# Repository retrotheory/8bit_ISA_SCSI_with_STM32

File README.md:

# 8bit_ISA_SCSI_with_STM32
ISA SCSI card with BIOS and spot of software SCSI emulation with STM32

SCSI card designed from the NCR53C400 Technical Document

More details to come

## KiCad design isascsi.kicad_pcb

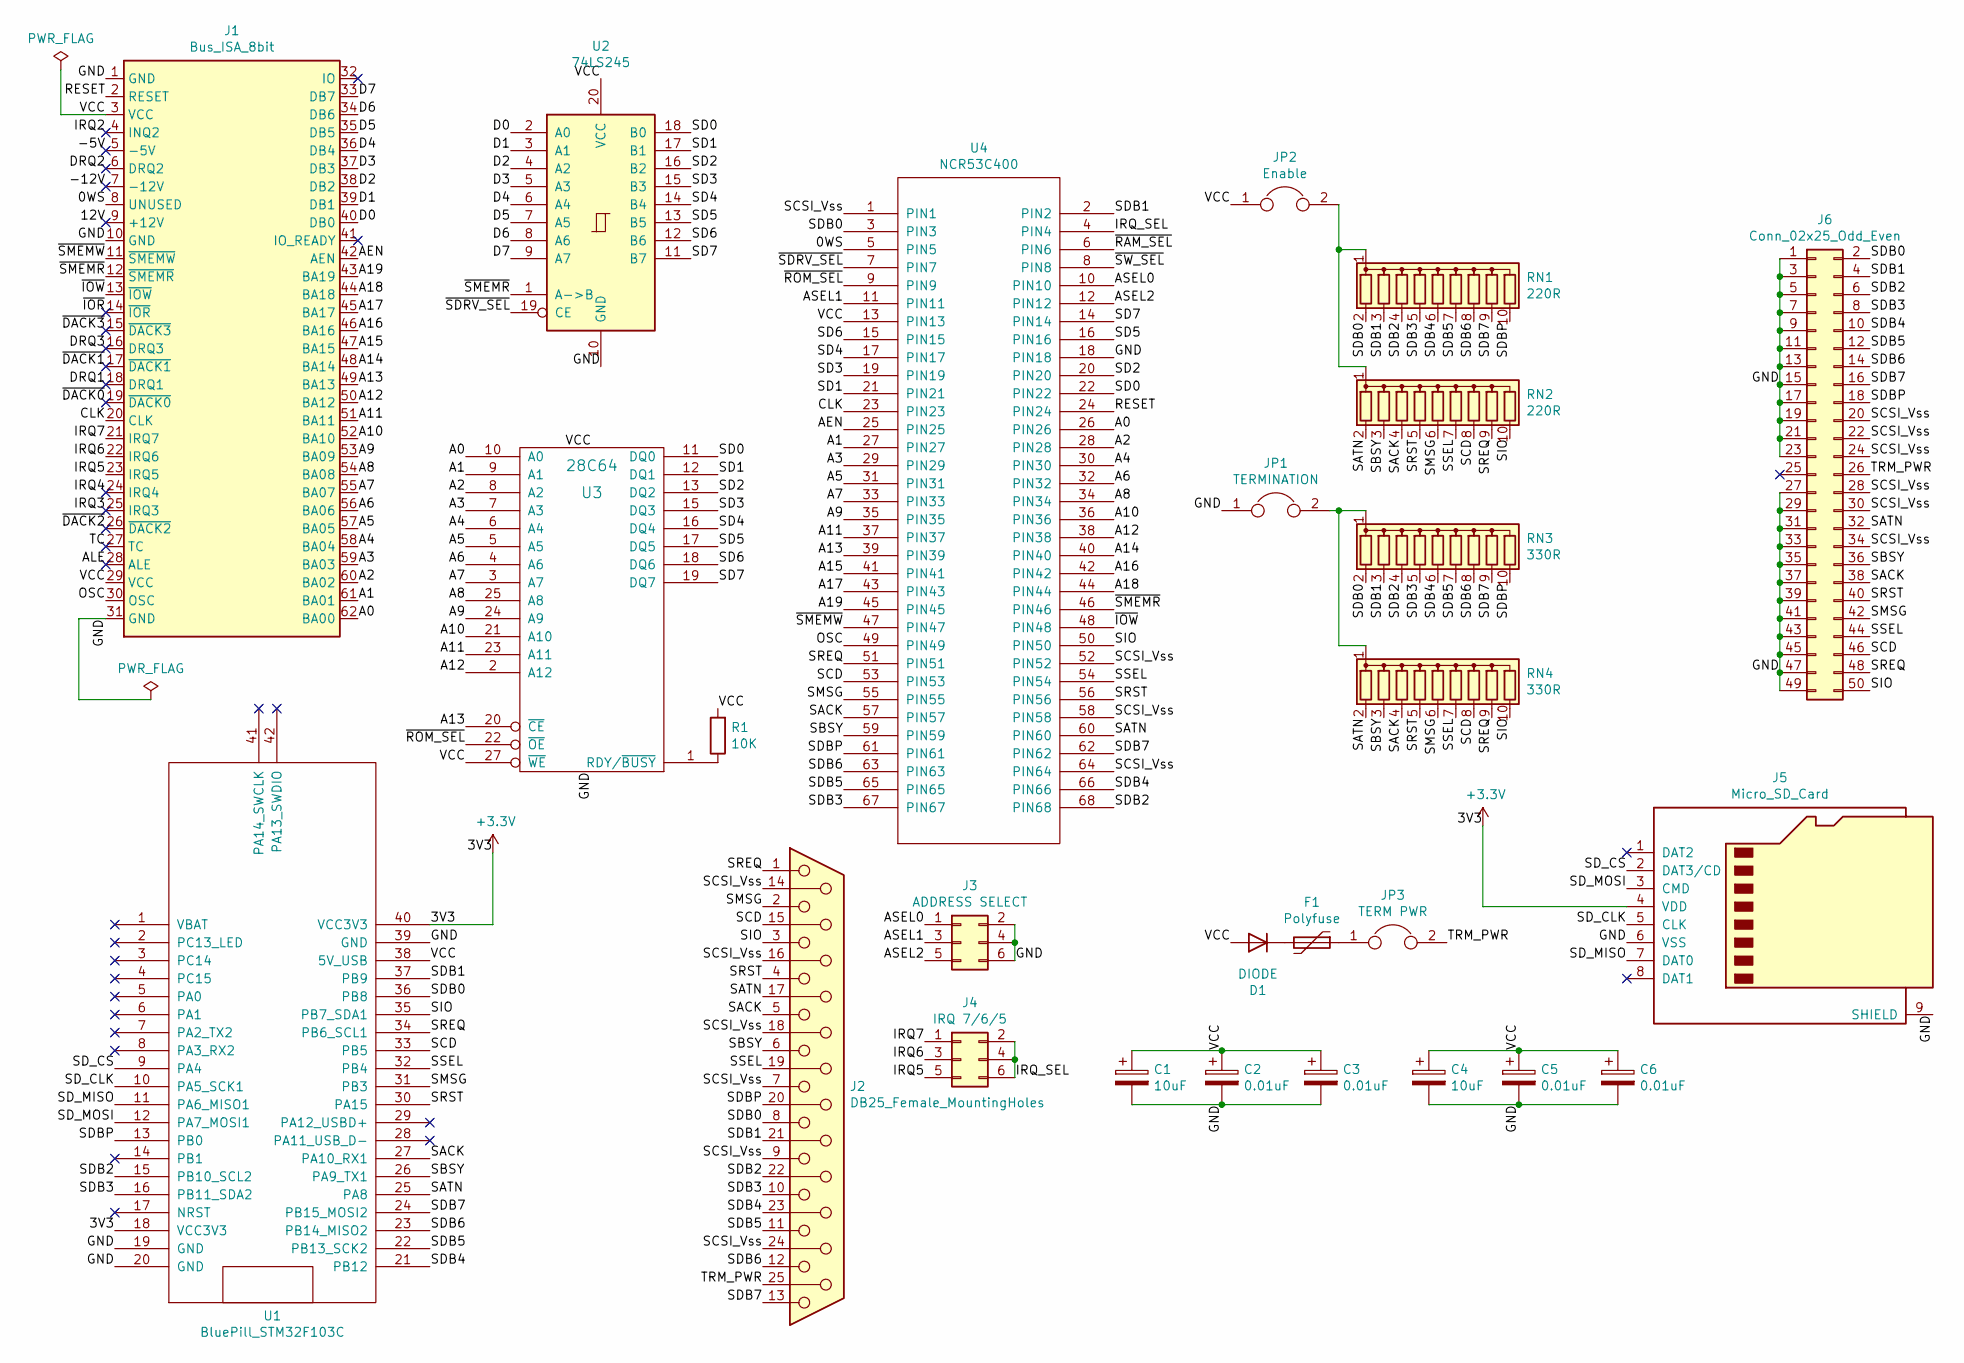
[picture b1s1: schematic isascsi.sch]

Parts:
C1, C4: 10uF; CP_EIA-7343-31_Kemet-D_Pad2.25x2.55mm_HandSolder
C2, C3, C5, C6: 0.01uF; C_1206_3216Metric_Pad1.42x1.75mm_HandSolder
D1: DIODE; D_DO-201AD_P12.70mm_Horizontal
F1: Polyfuse; Fuse_1806_4516Metric_Pad1.57x1.80mm_HandSolder
J1: Bus_ISA_8bit; BUS_XT
J2: DB25_Female_MountingHoles; DSUB-25_Female_Horizontal_P2.77x2.84mm_EdgePinOffset4.94mm_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
J3: ADDRESS SELECT; PinHeader_2x03_P2.54mm_Vertical
J4: IRQ 7/6/5; PinHeader_2x03_P2.54mm_Vertical
J5: Micro_SD_Card; microSD_HC_Molex_104031-0811
J6: Conn_02x25_Odd_Even; IDC-Header_2x25_P2.54mm_Vertical
JP1: TERMINATION; PinHeader_1x02_P2.54mm_Vertical
JP2: Enable; PinHeader_1x02_P2.54mm_Vertical
JP3: TERM PWR; PinHeader_1x02_P2.54mm_Vertical
R1: 10K; R_1206_3216Metric
RN1, RN2: 220R; R_Array_SIP10
RN3, RN4: 330R; R_Array_SIP10
U1: BluePill_STM32F103C; YAAJ_BluePill_1
U2: 74LS245; IC_SOIC20_Wide
U3: 28C64; DIP-28_W15.24mm_Socket_LongPads
U4: NCR53C400; PLCC-68_THT-Socket

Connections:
+3V3: J5.4 (VDD), U1.18 (VCC3V3), U1.40 (VCC3V3)
/0WS: J1.8 (UNUSED), U4.5 (PIN5)
/12V: J1.9 (+12V)
/-5V: J1.5 (-5V)
/-12V: J1.7 (-12V)
/A0: J1.62 (BA00), U3.10 (A0), U4.26 (PIN26)
/A1: J1.61 (BA01), U3.9 (A1), U4.27 (PIN27)
/A2: J1.60 (BA02), U3.8 (A2), U4.28 (PIN28)
/A3: J1.59 (BA03), U3.7 (A3), U4.29 (PIN29)
/A4: J1.58 (BA04), U3.6 (A4), U4.30 (PIN30)
/A5: J1.57 (BA05), U3.5 (A5), U4.31 (PIN31)
/A6: J1.56 (BA06), U3.4 (A6), U4.32 (PIN32)
/A7: J1.55 (BA07), U3.3 (A7), U4.33 (PIN33)
/A8: J1.54 (BA08), U3.25 (A8), U4.34 (PIN34)
/A9: J1.53 (BA09), U3.24 (A9), U4.35 (PIN35)
/A10: J1.52 (BA10), U3.21 (A10), U4.36 (PIN36)
/A11: J1.51 (BA11), U3.23 (A11), U4.37 (PIN37)
/A12: J1.50 (BA12), U3.2 (A12), U4.38 (PIN38)
/A13: J1.49 (BA13), U3.20 (~CE), U4.39 (PIN39)
/A14: J1.48 (BA14), U4.40 (PIN40)
/A15: J1.47 (BA15), U4.41 (PIN41)
/A16: J1.46 (BA16), U4.42 (PIN42)
/A17: J1.45 (BA17), U4.43 (PIN43)
/A18: J1.44 (BA18), U4.44 (PIN44)
/A19: J1.43 (BA19), U4.45 (PIN45)
/AEN: J1.42 (AEN), U4.25 (PIN25)
/ALE: J1.28 (ALE)
/ASEL0: J3.1, U4.10 (PIN10)
/ASEL1: J3.3, U4.11 (PIN11)
/ASEL2: J3.5, U4.12 (PIN12)
/CLK: J1.20 (CLK), U4.23 (PIN23)
/D0: J1.40 (DB0), U2.2 (A0)
/D1: J1.39 (DB1), U2.3 (A1)
/D2: J1.38 (DB2), U2.4 (A2)
/D3: J1.37 (DB3), U2.5 (A3)
/D4: J1.36 (DB4), U2.6 (A4)
/D5: J1.35 (DB5), U2.7 (A5)
/D6: J1.34 (DB6), U2.8 (A6)
/D7: J1.33 (DB7), U2.9 (A7)
/DRQ1: J1.18 (DRQ1)
/DRQ2: J1.6 (DRQ2)
/DRQ3: J1.16 (DRQ3)
/IRQ2: J1.4 (INQ2)
/IRQ3: J1.25 (IRQ3)
/IRQ4: J1.24 (IRQ4)
/IRQ5: J1.23 (IRQ5), J4.5
/IRQ6: J1.22 (IRQ6), J4.3
/IRQ7: J1.21 (IRQ7), J4.1
/IRQ_SEL: J4.2, J4.4, J4.6, U4.4 (PIN4)
/OSC: J1.30 (OSC), U4.49 (PIN49)
/RESET: J1.2 (RESET), U4.24 (PIN24)
/SACK: J2.5, J6.38, RN2.4 (R3), RN4.4 (R3), U1.27 (PA10_RX1), U4.57 (PIN57)
/SATN: J2.17, J6.32, RN2.2 (R1), RN4.2 (R1), U1.25 (PA8), U4.60 (PIN60)
/SBSY: J2.6, J6.36, RN2.3 (R2), RN4.3 (R2), U1.26 (PA9_TX1), U4.59 (PIN59)
/SCD: J2.15, J6.46, RN2.8 (R7), RN4.8 (R7), U1.33 (PB5), U4.53 (PIN53)
/SCSI_Vss: J2.7, J2.9, J2.14, J2.16, J2.18, J2.24, J6.20, J6.22, J6.24, J6.28, J6.30, J6.34, U4.1 (PIN1), U4.52 (PIN52), U4.58 (PIN58), U4.64 (PIN64)
/SD0: U2.18 (B0), U3.11 (DQ0), U4.22 (PIN22)
/SD1: U2.17 (B1), U3.12 (DQ1), U4.21 (PIN21)
/SD2: U2.16 (B2), U3.13 (DQ2), U4.20 (PIN20)
/SD3: U2.15 (B3), U3.15 (DQ3), U4.19 (PIN19)
/SD4: U2.14 (B4), U3.16 (DQ4), U4.17 (PIN17)
/SD5: U2.13 (B5), U3.17 (DQ5), U4.16 (PIN16)
/SD6: U2.12 (B6), U3.18 (DQ6), U4.15 (PIN15)
/SD7: U2.11 (B7), U3.19 (DQ7), U4.14 (PIN14)
/SDB0: J2.8, J6.2, RN1.2 (R1), RN3.2 (R1), U1.36 (PB8), U4.3 (PIN3)
/SDB1: J2.21, J6.4, RN1.3 (R2), RN3.3 (R2), U1.37 (PB9), U4.2 (PIN2)
/SDB2: J2.22, J6.6, RN1.4 (R3), RN3.4 (R3), U1.15 (PB10_SCL2), U4.68 (PIN68)
/SDB3: J2.10, J6.8, RN1.5 (R4), RN3.5 (R4), U1.16 (PB11_SDA2), U4.67 (PIN67)
/SDB4: J2.23, J6.10, RN1.6 (R5), RN3.6 (R5), U1.21 (PB12), U4.66 (PIN66)
/SDB5: J2.11, J6.12, RN1.7 (R6), RN3.7 (R6), U1.22 (PB13_SCK2), U4.65 (PIN65)
/SDB6: J2.12, J6.14, RN1.8 (R7), RN3.8 (R7), U1.23 (PB14_MISO2), U4.63 (PIN63)
/SDB7: J2.13, J6.16, RN1.9 (R8), RN3.9 (R8), U1.24 (PB15_MOSI2), U4.62 (PIN62)
/SDBP: J2.20, J6.18, RN1.10 (R9), RN3.10 (R9), U1.13 (PB0), U4.61 (PIN61)
/SD_CLK: J5.5 (CLK), U1.10 (PA5_SCK1)
/SD_CS: J5.2 (DAT3/CD), U1.9 (PA4)
/SD_MISO: J5.7 (DAT0), U1.11 (PA6_MISO1)
/SD_MOSI: J5.3 (CMD), U1.12 (PA7_MOSI1)
/SIO: J2.3, J6.50, RN2.10 (R9), RN4.10 (R9), U1.35 (PB7_SDA1), U4.50 (PIN50)
/SMSG: J2.2, J6.42, RN2.6 (R5), RN4.6 (R5), U1.31 (PB3), U4.55 (PIN55)
/SREQ: J2.1, J6.48, RN2.9 (R8), RN4.9 (R8), U1.34 (PB6_SCL1), U4.51 (PIN51)
/SRST: J2.4, J6.40, RN2.5 (R4), RN4.5 (R4), U1.30 (PA15), U4.56 (PIN56)
/SSEL: J2.19, J6.44, RN2.7 (R6), RN4.7 (R6), U1.32 (PB4), U4.54 (PIN54)
/TC: J1.27 (TC)
/~DACK0: J1.19 (~DACK0)
/~DACK1: J1.17 (~DACK1)
/~DACK2: J1.26 (~DACK2)
/~DACK3: J1.15 (~DACK3)
/~IOR: J1.14 (~IOR)
/~IOW: J1.13 (~IOW), U4.48 (PIN48)
/~RAM_SEL: U4.6 (PIN6)
/~ROM_SEL: U3.22 (~OE), U4.9 (PIN9)
/~SDRV_SEL: U2.19 (CE), U4.7 (PIN7)
/~SMEMR: J1.12 (~SMEMR), U2.1 (A->B), U4.46 (PIN46)
/~SMEMW: J1.11 (~SMEMW), U4.47 (PIN47)
/~SW_SEL: U4.8 (PIN8)
GND: C1.2, C2.2, C3.2, C4.2, C5.2, C6.2, J1.1 (GND), J1.10 (GND), J1.31 (GND), J3.2, J3.4, J3.6, J5.6 (VSS), J5.9 (SHIELD), J6.1, J6.3, J6.5, J6.7, J6.9, J6.11, J6.13, J6.15, J6.17, J6.19, J6.21, J6.23, J6.27, J6.29, J6.31, J6.33, J6.35, J6.37, J6.39, J6.41, J6.43, J6.45, J6.47, J6.49, JP1.1, U1.19 (GND), U1.20 (GND), U1.39 (GND), U2.10 (GND), U3.14 (GND), U4.18 (PIN18)
unnamed: D1.1 (K), F1.2
unnamed: JP1.2, RN3.1 (common), RN4.1 (common)
unnamed: JP2.2, RN1.1 (common), RN2.1 (common)
unnamed: R1.1, U3.1 (RDY/~BUSY)
VCC: C1.1, C2.1, C3.1, C4.1, C5.1, C6.1, D1.2 (A), J1.3 (VCC), J1.29 (VCC), JP2.1, R1.2, U1.38 (5V_USB), U2.20 (VCC), U3.27 (~WE), U3.28 (VCC), U4.13 (PIN13)

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
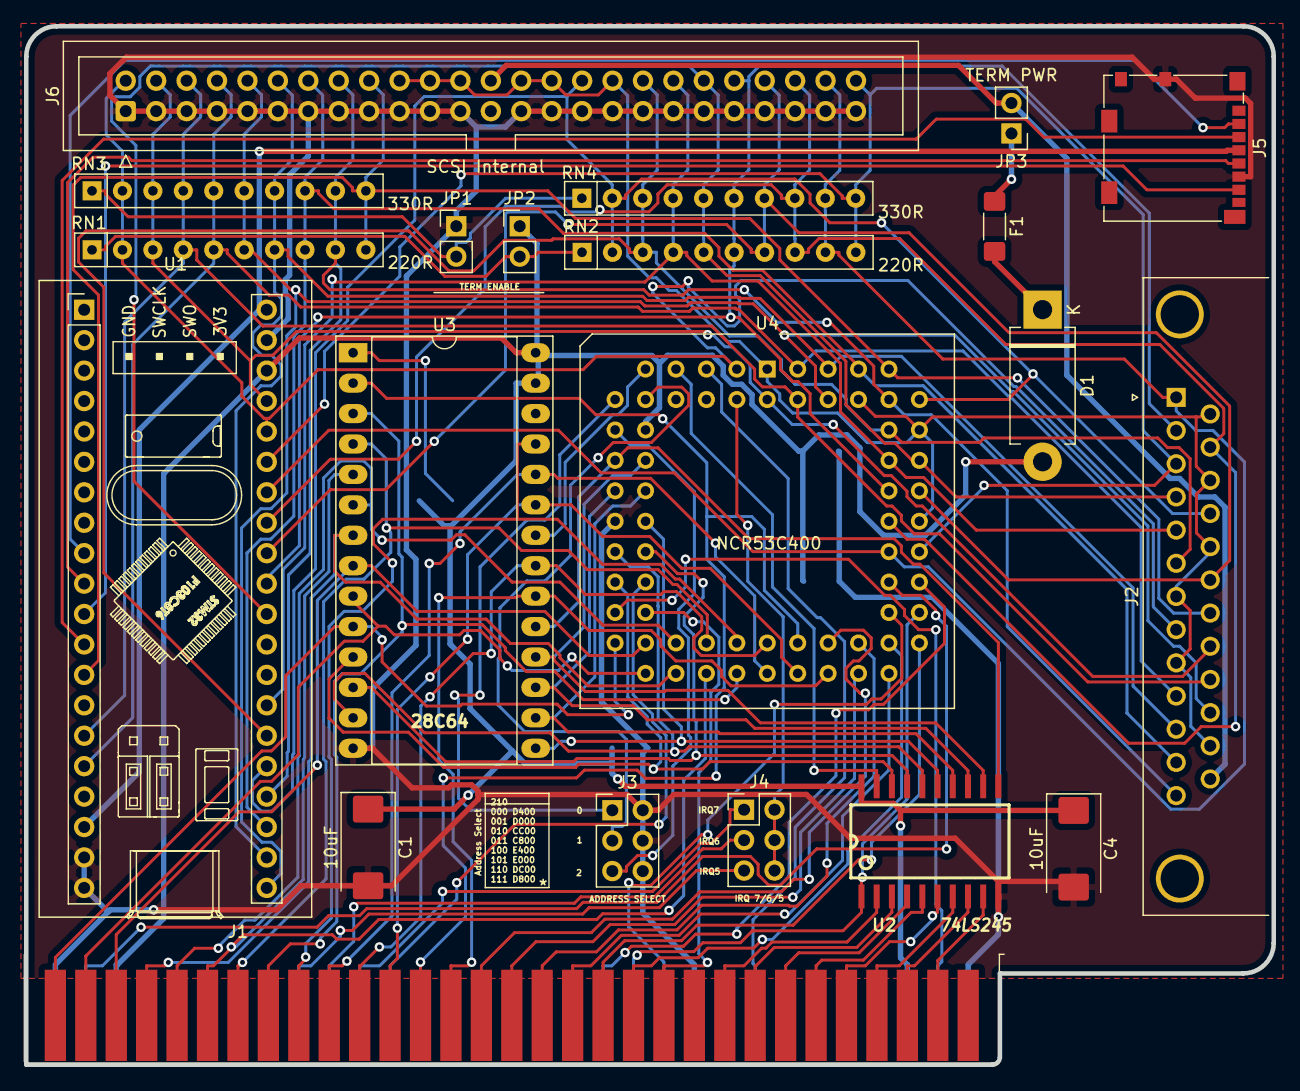
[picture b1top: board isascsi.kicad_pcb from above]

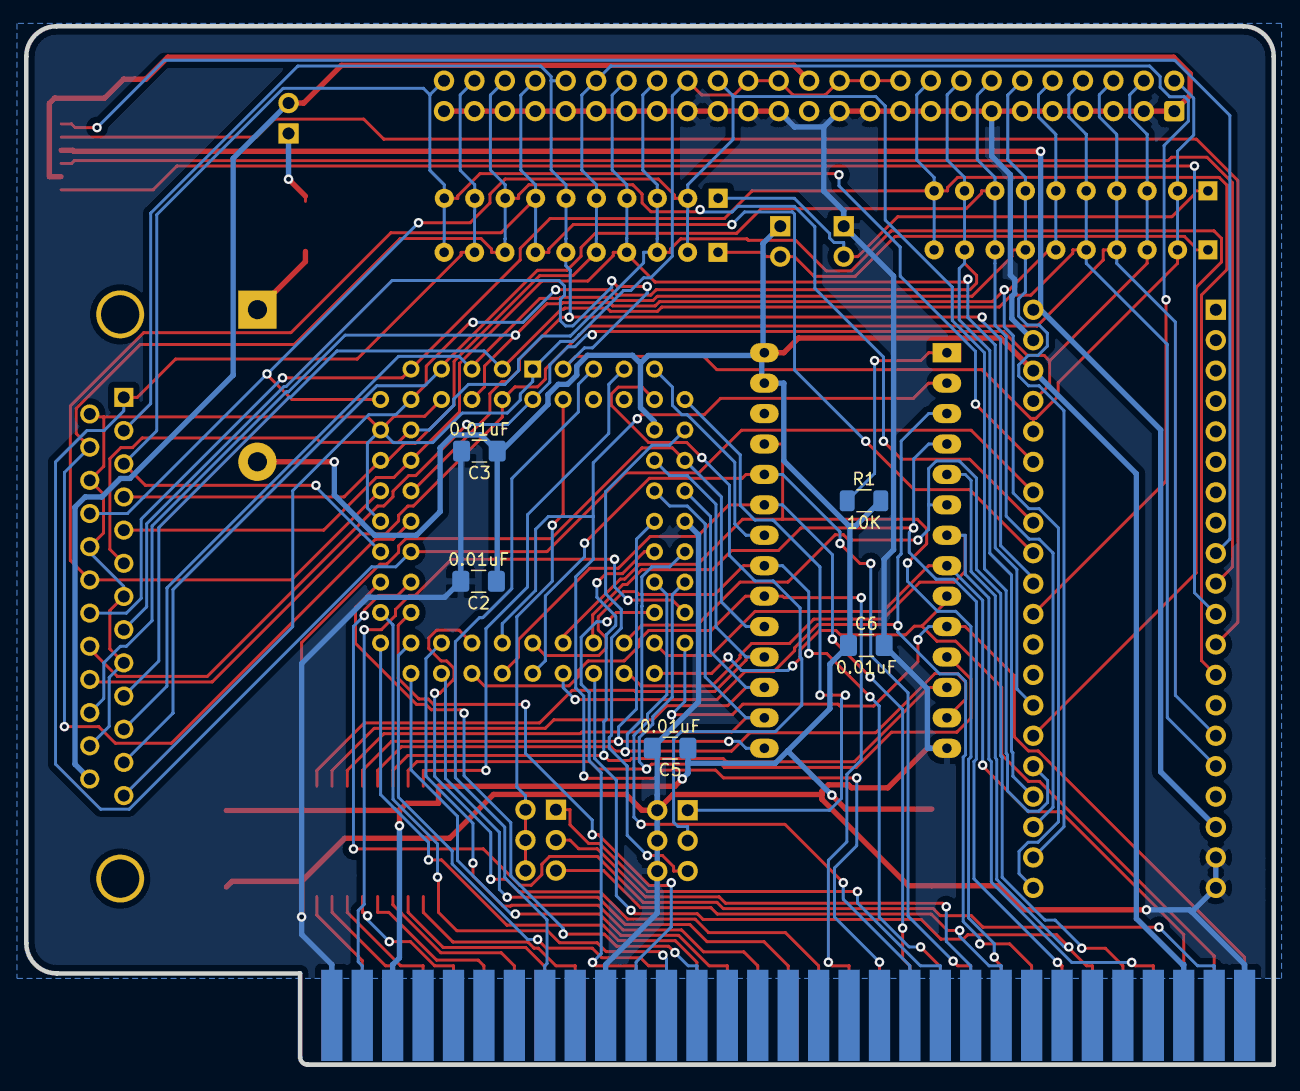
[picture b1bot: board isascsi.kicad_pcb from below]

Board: 2 copper layers, 104.1 x 86.7 mm, 26 parts (5 on the bottom side), 84 nets.
